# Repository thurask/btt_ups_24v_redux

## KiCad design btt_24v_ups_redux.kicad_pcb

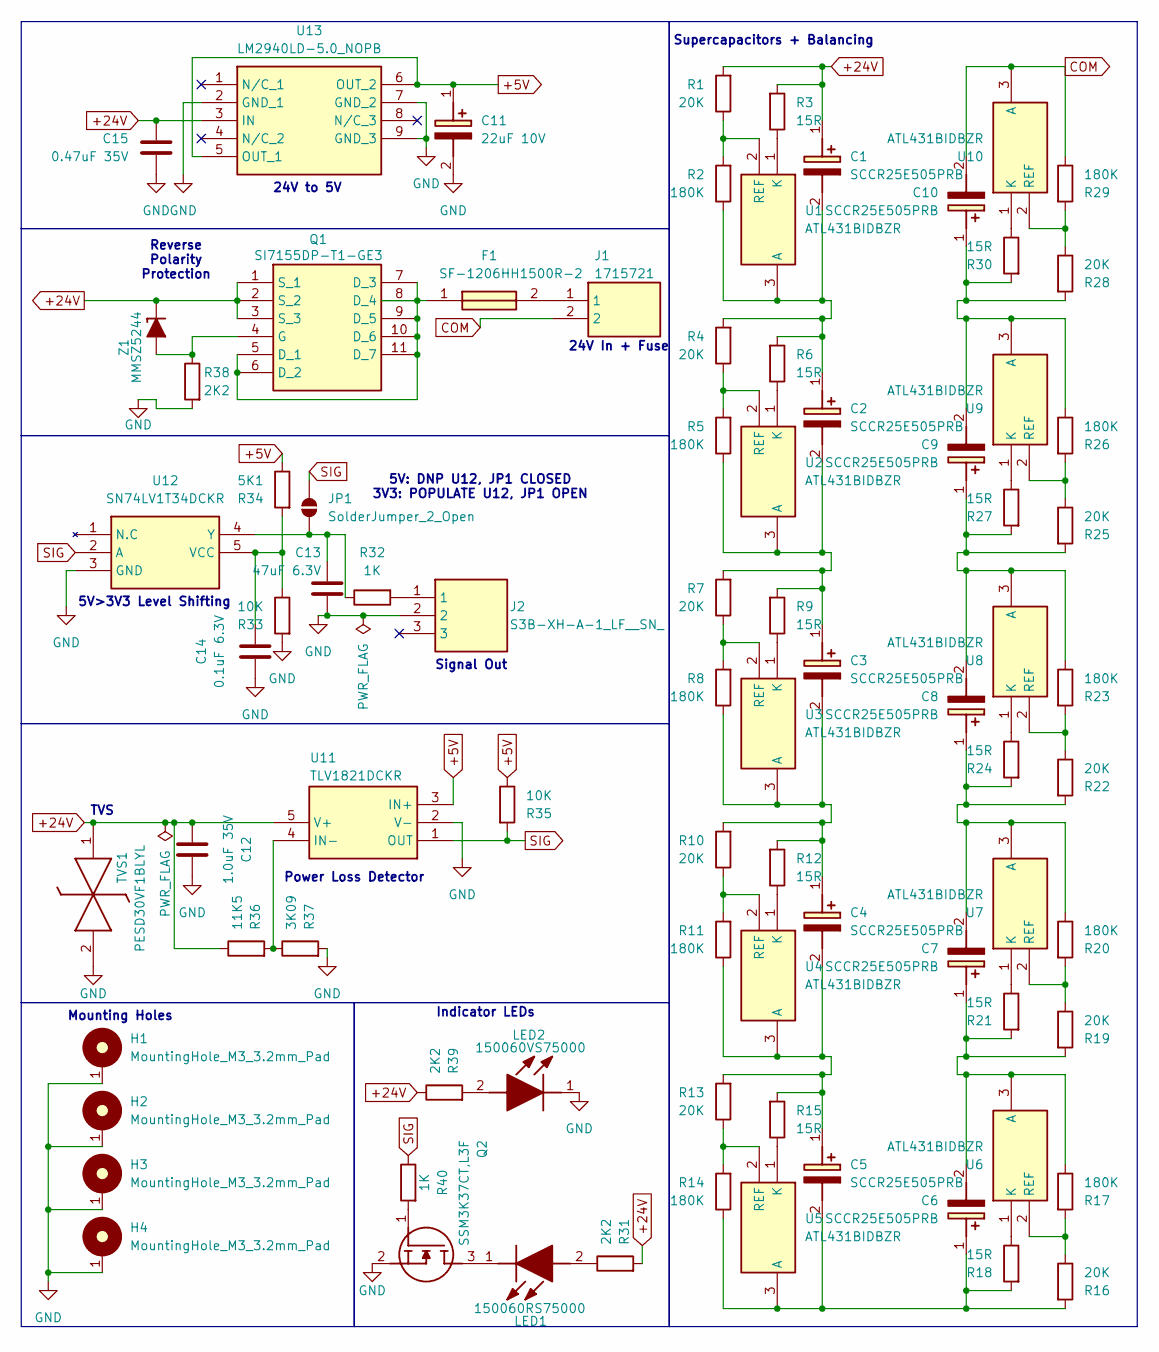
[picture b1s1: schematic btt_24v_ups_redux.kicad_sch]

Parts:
C1, C2, C3, C4, C5, C6, C7, C8, C9, C10: SCCR25E505PRB; CAPPRD350W65D800H2650; Mouser Part Number 581-SCCR25E505PRB
C11: 22uF 10V; T529P; Mouser Part Number 80-T529P226M10AAE200
C12: 1.0uF 35V; C_0603_1608Metric
C13: 47uF 6.3V; C_0603_1608Metric
C14: 0.1uF 6.3V; C_0603_1608Metric
C15: 0.47uF 35V; C_0603_1608Metric
F1: SF-1206HH1500R-2; SF1206HH1500R2; Mouser Part Number 652-SF-1206HH1500R-2
H1, H2, H3, H4: MountingHole_M3_3.2mm_Pad; MountingHole_3.2mm_Pad
J1: 1715721; Mouser Part Number 651-1715721
J2: S3B-XH-A-1_LF__SN_; SHDRRA3W64P0X250_1X3_990X1150X610P; Manufacturer_Part_Number S3B-XH-A-1(LF)(SN)
JP1: SolderJumper_2_Open; SolderJumper-2_P1.3mm_Open_TrianglePad1.0x1.5mm
LED1: 150060RS75000; LEDC1608X80N; Mouser Part Number 710-150060RS75000
LED2: 150060VS75000; LEDC1608X80N; Mouser Part Number 710-150060VS75000
Q1: SI7155DP-T1-GE3; SI7155DPT1GE3; Mouser Part Number 78-SISH101DN-T1-GE3
Q2: SSM3K37CT,L3F; SOT50P160X90-3N; Manufacturer_Part_Number DMN313DLT-7
R1, R4, R7, R10, R13, R16, R19, R22, R25, R28: 20K; R_0805_2012Metric
R2, R5, R8, R11, R14, R17, R20, R23, R26, R29: 180K; R_0805_2012Metric
R3, R6, R9, R12, R15, R18, R21, R24, R27, R30: 15R; R_0805_2012Metric
R31, R38, R39: 2K2; R_0603_1608Metric
R32, R40: 1K; R_0603_1608Metric
R33, R35: 10K; R_0603_1608Metric
R34: 5K1; R_0603_1608Metric
R36: 11K5; R_0603_1608Metric
R37: 3K09; R_0603_1608Metric
TVS1: PESD30VF1BLYL; PESD5V0S1BL315; Manufacturer_Part_Number PESD30VF1BLYL
U1, U2, U3, U4, U5, U6, U7, U8, U9, U10: ATL431BIDBZR; SOT95P237X112-3N; Mouser Part Number 595-ATL431BIDBZR
U11: TLV1821DCKR; SOT65P210X110-5N; Mouser Part Number 595-TLV1821DCKR
U12: SN74LV1T34DCKR; SOT65P210X110-5N; Mouser Part Number 595-SN74LV1T34DCKR
U13: LM2940LD-5.0_NOPB; LM2940LD50NOPB; Mouser Part Number 926-LM2940LD50NOPB
Z1: MMSZ5244; D_SOD-123; Manufacturer_Part_Number YFZVFHTR10B

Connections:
+5V: C11.1 (+), R34.2, R35.2, U11.3 (IN+), U13.5 (OUT_1), U13.6 (OUT_2)
+24V: C1.1 (+), C12.1, C15.1, Q1.1 (S_1), Q1.2 (S_2), Q1.3 (S_3), R1.1, R3.1, R31.1, R36.2, R39.2, TVS1.1 (K1), U11.5 (V+), U13.3 (IN), Z1.1 (K)
COM: C10.2 (-), J1.2, R29.2, U10.3 (A)
GND: C11.2 (-), C12.2, C13.2, C14.2, C15.2, H1.1, H2.1, H3.1, H4.1, J2.2, LED2.1 (K), Q2.2 (S), R33.1, R37.1, R38.1, TVS1.2 (K2), U11.2 (V-), U12.3 (GND), U13.2 (GND_1), U13.7 (GND_2), U13.9 (GND_3)
unnamed: C1.2 (-), C2.1 (+), R2.2, R4.1, R6.1, U1.3 (A)
unnamed: C2.2 (-), C3.1 (+), R5.2, R7.1, R9.1, U2.3 (A)
unnamed: C3.2 (-), C4.1 (+), R8.2, R10.1, R12.1, U3.3 (A)
unnamed: C4.2 (-), C5.1 (+), R11.2, R13.1, R15.1, U4.3 (A)
unnamed: C5.2 (-), C6.1 (+), R14.2, R16.1, R18.1, U5.3 (A)
unnamed: C6.2 (-), C7.1 (+), R17.2, R19.1, R21.1, U6.3 (A)
unnamed: C7.2 (-), C8.1 (+), R20.2, R22.1, R24.1, U7.3 (A)
unnamed: C8.2 (-), C9.1 (+), R23.2, R25.1, R27.1, U8.3 (A)
unnamed: C9.2 (-), C10.1 (+), R26.2, R28.1, R30.1, U9.3 (A)
unnamed: F1.2, J1.1
unnamed: J2.1, R32.1
unnamed: C13.1, JP1.2 (B), R32.2, U12.4 (Y)
unnamed: LED1.2 (A), R31.2
unnamed: LED1.1 (K), Q2.3 (D)
unnamed: LED2.2 (A), R39.1
unnamed: F1.1, Q1.5 (D_1), Q1.6 (D_2), Q1.7 (D_3), Q1.8 (D_4), Q1.9 (D_5), Q1.10 (D_6), Q1.11 (D_7)
unnamed: Q1.4 (G), R38.2, Z1.2 (A)
unnamed: Q2.1 (G), R40.1
unnamed: R3.2, U1.1 (K)
unnamed: R1.2, R2.1, U1.2 (REF)
unnamed: R6.2, U2.1 (K)
unnamed: R4.2, R5.1, U2.2 (REF)
unnamed: R9.2, U3.1 (K)
unnamed: R7.2, R8.1, U3.2 (REF)
unnamed: R12.2, U4.1 (K)
unnamed: R10.2, R11.1, U4.2 (REF)
unnamed: R15.2, U5.1 (K)
unnamed: R13.2, R14.1, U5.2 (REF)
unnamed: R18.2, U6.1 (K)
unnamed: R16.2, R17.1, U6.2 (REF)
unnamed: R21.2, U7.1 (K)
unnamed: R19.2, R20.1, U7.2 (REF)
unnamed: R24.2, U8.1 (K)
unnamed: R22.2, R23.1, U8.2 (REF)
unnamed: R27.2, U9.1 (K)
unnamed: R25.2, R26.1, U9.2 (REF)
unnamed: R30.2, U10.1 (K)
unnamed: R28.2, R29.1, U10.2 (REF)
unnamed: R36.1, R37.2, U11.4 (IN-)
unnamed: C14.1, R33.2, R34.1, U12.5 (VCC)
SIG: JP1.1 (A), R35.1, R40.2, U11.1 (OUT), U12.2 (A)

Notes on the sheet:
Supercapacitors + Balancing
Signal Out
Indicator LEDs
5V: DNP U12, JP1 CLOSED 3V3: POPULATE U12, JP1 OPEN
Mounting Holes
5V>3V3 Level Shifting
24V In + Fuse
Reverse Polarity Protection
Power Loss Detector
TVS
24V to 5V

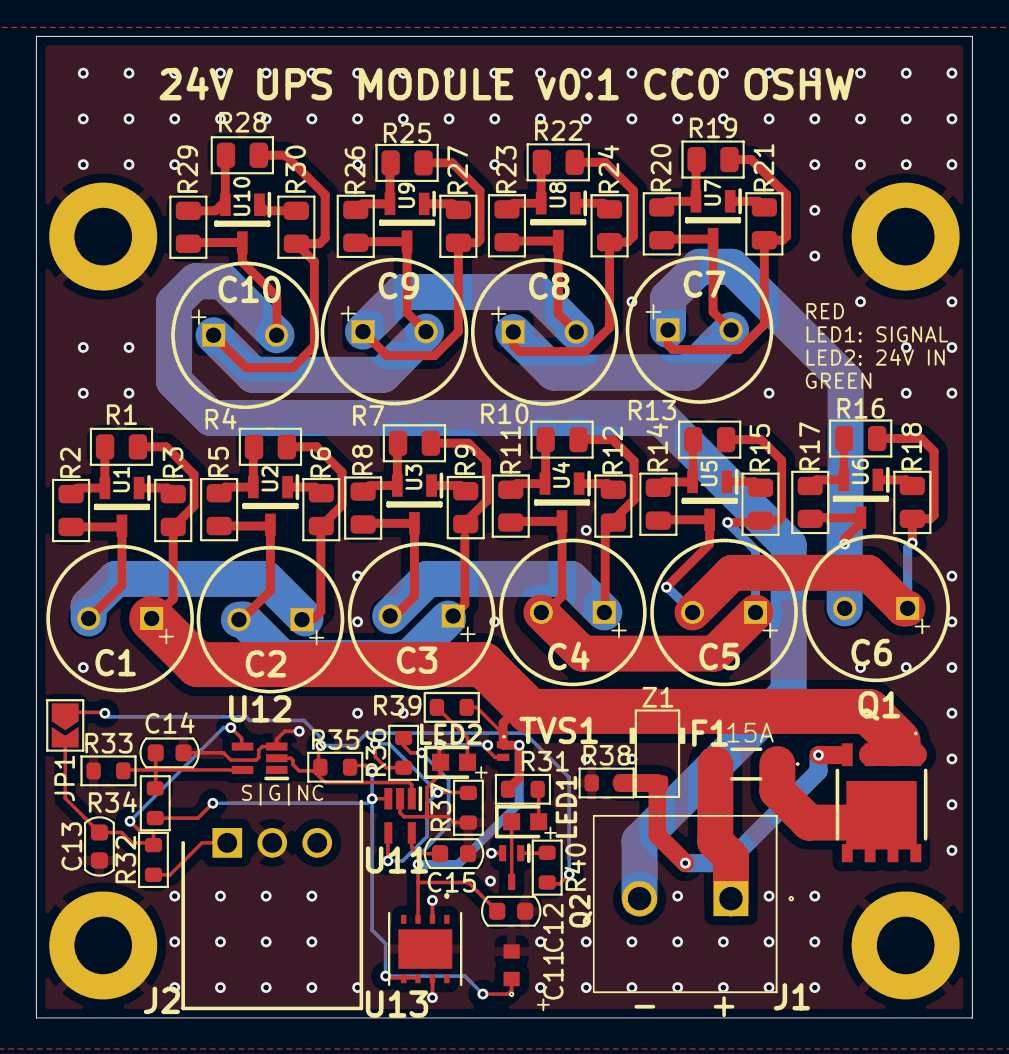
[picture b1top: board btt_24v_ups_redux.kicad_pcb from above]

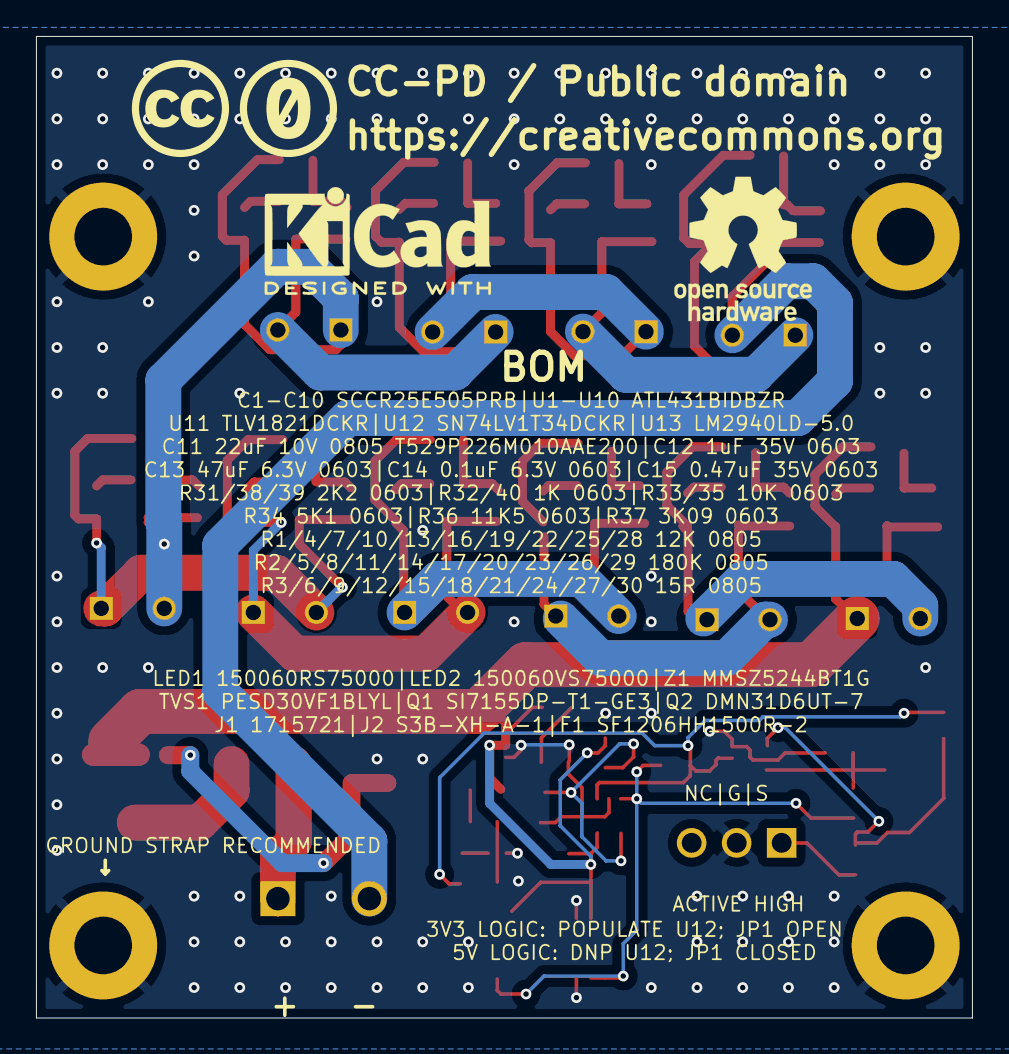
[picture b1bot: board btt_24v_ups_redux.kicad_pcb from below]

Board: 2 copper layers, 52.0 x 54.5 mm, 85 parts (3 on the bottom side), 45 nets.

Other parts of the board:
L01: OSHW-Logo_7.5x8mm_SilkScreen
L02: Symbol_CreativeCommonsPublicDomain_SilkScreenTop_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; Symbol_CreativeCommonsPublicDomain_SilkScreenTop_Small
L03: KiCad-Logo2_5mm_SilkScreen

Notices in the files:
btt_24v_ups_redux.kicad_pcb:
24V UPS MODULE v0.1 CC0 OSHW
parts and their libraries:
CC-PD / Public domain
